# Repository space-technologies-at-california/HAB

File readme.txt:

High Altitude Balloon Team
Space Technologies at Cal
University of California, Berkeley

We're currently working on HABV!

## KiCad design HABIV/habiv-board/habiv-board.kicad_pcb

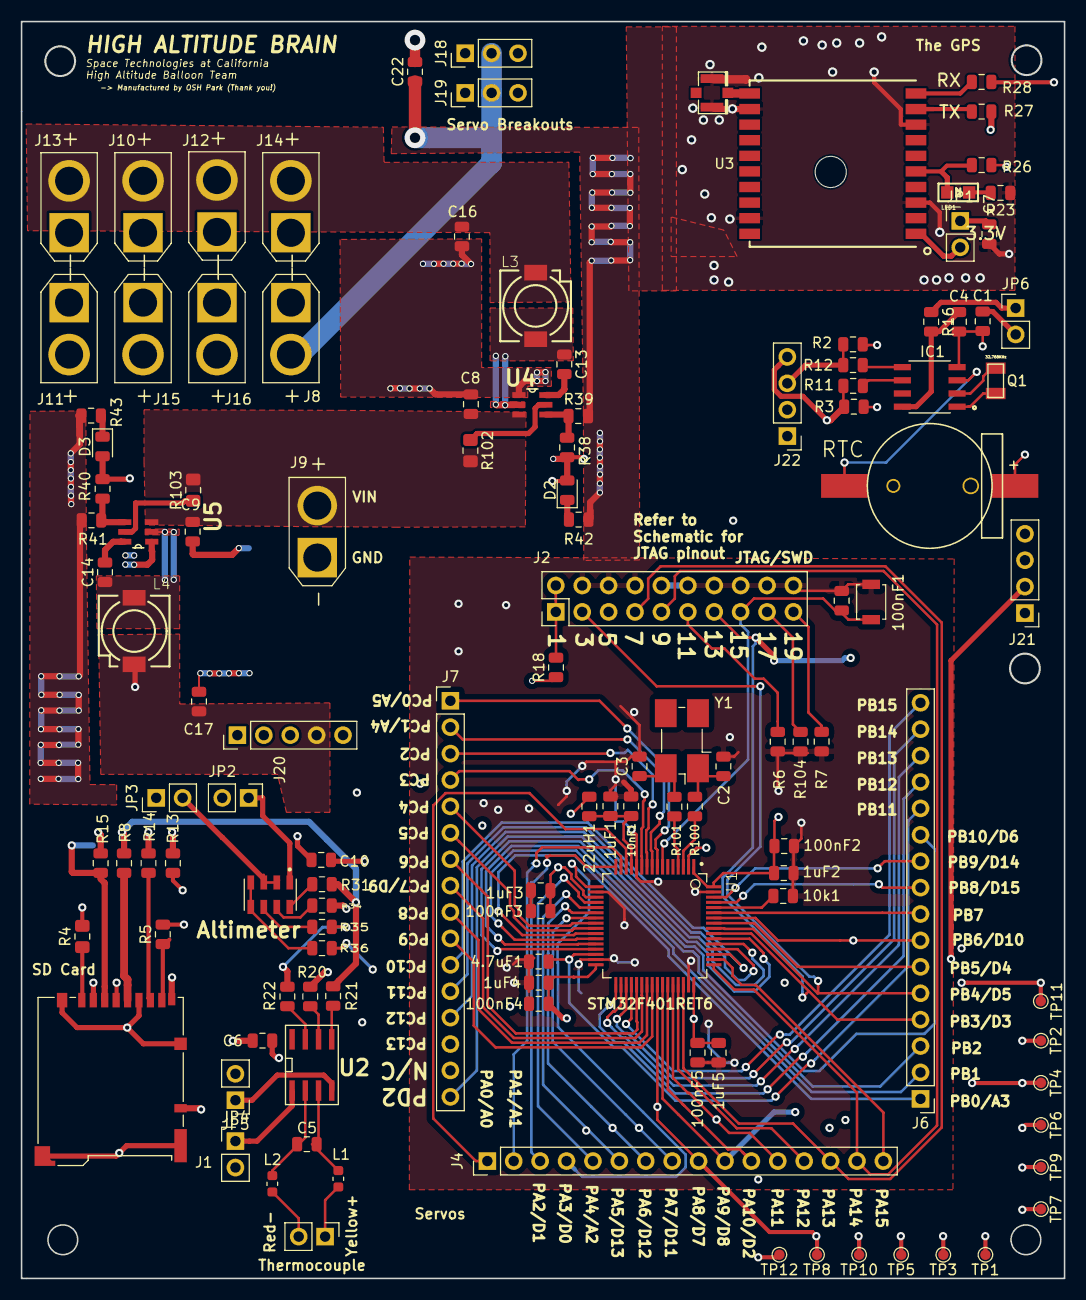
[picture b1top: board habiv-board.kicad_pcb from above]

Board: 4 copper layers, 100.3 x 120.9 mm, 122 parts (0 on the bottom side), 106 nets.

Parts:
1uF1: C6; C_0805_2012Metric
1uF2: C14; C_0805_2012Metric
1uF3: C8; C_0805_2012Metric
1uF4: C12; C_0805_2012Metric
1uF5: C10; C_0805_2012Metric
4.7uF1: C21; C_0805_2012Metric
10k1: R5; R_0805_2012Metric
10nF1: C7; C_0805_2012Metric
22uH1: L1; L_0805_2012Metric
100nF1: C5; C_0805_2012Metric
100nF2: C15; C_0805_2012Metric
100nF3: C9; C_0805_2012Metric
100nF4: C13; C_0805_2012Metric
100nF5: C11; C_0805_2012Metric
B2: CR1220; S8411-45R
C1, C22: 10u; C_0805_2012Metric
C2, C3: 4.3pF; C_0805_2012Metric
C4: 3.3uF; C_0805_2012Metric
C5: .01 uF; C_0805_2012Metric
C6: 0.1 uF; C_0805_2012Metric
C7: 0.1u; C_0805_2012Metric
C8, C9: 10uF; C_0805_2012Metric
C10, C13, C14: 100nF; C_0805_2012Metric
C16, C17: 47uF; C_0805_2012Metric
D2, D3: LED; LED_0805_2012Metric
IC1: RTC_PCF8523T; SOIC127P600X175-8N
J1: Micro_SD_Card_Det; microSD_HC_Hirose_DM3BT-DSF-PEJS
J2: Conn_ARM_JTAG_SWD_20; PinHeader_2x10_P2.54mm_Vertical
J3: Conn_01x02_Male; PinHeader_1x02_P2.54mm_Vertical
J4, J6, J7: Conn_01x16_Male; PinHeader_1x16_P2.54mm_Vertical
J8, J10, J11, J12, J13, J14, J15, J16: Conn_01x02_Female; AMASS_XT30U-F_1x02_P5.0mm_Vertical
J9: Conn_01x02_Male; AMASS_XT30U-M_1x02_P5.0mm_Vertical
J18, J19: Conn_01x03_Male; PinHeader_1x03_P2.54mm_Vertical
J20: Conn_01x05_Male; PinHeader_1x05_P2.54mm_Vertical
J21, J22: Conn_01x04_Male; PinHeader_1x04_P2.54mm_Vertical
JP1, JP2, JP3, JP4, JP5, JP6: Jumper; PinHeader_1x02_P2.54mm_Vertical
L1, L2: Ferrite_Bead; L_0603_1608Metric
L3: 2.2uH; INDC7070X450
L4: 3.3uH; INDC7070X450
LED1: RED; CHIPLED_0805
Q1: 32.768KHz; XTAL320X150X90
R2, R3: 8.2k; R_0805_2012Metric
R4: 0; R_0805_2012Metric_Pad1.15x1.40mm_HandSolder
R5, R8, R11, R12, R13, R14, R15, R18, R20, R21, R22, R26, R27, R28, R31, R34, R35, R36: 0; R_0805_2012Metric
R6, R7, R104: 10K; R_0805_2012Metric
R16, R23: 1K; R_0805_2012Metric
R38: 33.2k; R_0805_2012Metric
R39, R41: 10k; R_0805_2012Metric
R40: 56.2k; R_0805_2012Metric
R42, R43: 4.7k; R_0805_2012Metric
R100: 0k1; R_0805_2012Metric
R101: 0k2; R_0805_2012Metric
R102, R103: 10K; R_0805_2012Metric_Pad1.15x1.40mm_HandSolder
SW1: SW_DPST_x2; SW_SPST_B3U-1000P
TP1, TP2, TP3, TP4, TP5, TP6, TP7, TP8, TP9, TP10, TP11, TP12: TestPoint; TestPoint_Pad_D1.0mm
U1: STM32F401RET6; QFP50P1200X1200X160-64N
U2: MAX31855; SO-8
U3: FGPMMOPA6H
U4, U5: TPS564208
U7: MS560702BA03-00; SON125P500X300X100-8N
U$1: U.FL
Y1: 32.768MHz; Crystal_SMD_0603-4Pin_6.0x3.5mm_HandSoldering

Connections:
+3V3: 1uF2.2, 1uF3.2, 1uF4.2, 1uF5.2, 22uH1.2, 100nF2.2, 100nF3.2, 100nF4.2, 100nF5.2, C1.1, C6.2, C7.1, C10.1, C16.1, D2.2, J1.4, J10.2, J12.2, J13.2, J14.2, J21.4, J22.2, JP1.1, JP2.2, JP5.2, JP6.2, L3.1, R2.1, R3.1, R4.2, R5.2, R18.1, R38.2, U1.1, U1.19, U1.32, U1.48, U1.64
+5V: C17.1, C22.1, D3.2, J8.2, J11.2, J15.2, J16.2, J18.2, J19.2, J20.4, L4.1, R40.2
GND: 1uF1.1, 1uF2.1, 1uF3.1, 1uF4.1, 1uF5.1, 4.7uF1.1, 10k1.2, 10nF1.1, 100nF1.2, 100nF2.1, 100nF3.1, 100nF4.1, 100nF5.1, B2.1, C1.2, C2.2, C3.2, C4.2, C6.1, C7.2, C8.2, C9.2, C10.2, C16.2, C17.2, C22.2, IC1.4, J1.6, J1.11, J2.4, J2.6, J2.8, J2.10, J2.12, J2.14, J2.16, J2.18, J2.20, J8.1, J9.1, J10.1, J11.1, J12.1, J13.1, J14.1, J15.1, J16.1, J18.1, J19.1, J20.5, J21.1, J22.1, JP3.1, JP4.2, R6.1, R7.1, R23.1, R39.1, R41.1, R42.1, R43.1, R104.1, SW1.1, U1.12, U1.18, U1.31, U1.47, U1.63, U3.P$3, U3.P$8, U3.P$12, U3.P$19, U4.1, U5.1, U$1.P$1, U$1.P$2
unnamed: 10k1.1, U1.60
unnamed: 1uF1.2, 10nF1.2, 22uH1.1, U1.13
unnamed: B2.2, IC1.3
unnamed: C2.1, R100.2, Y1.1
unnamed: C3.1, R101.2, Y1.4
unnamed: C4.1, IC1.8, R16.2
unnamed: C5.1, L1.1, U2.3
unnamed: C5.2, L2.1, U2.2
unnamed: C8.1, C9.1, J9.2, R102.2, R103.2, U4.3, U5.3
unnamed: C13.1, L3.2, U4.2
unnamed: C13.2, U4.6
unnamed: C14.1, L4.2, U5.2
unnamed: C14.2, U5.6
unnamed: D2.1, R42.2
unnamed: D3.1, R43.2
unnamed: IC1.1, Q1.1
unnamed: IC1.2, Q1.2
unnamed: IC1.5, R12.1
unnamed: IC1.6, R11.1
unnamed: J1.1, R4.1
unnamed: J1.2, R13.2
unnamed: J1.3, R15.2
unnamed: J1.5, R8.1
unnamed: J1.7, R14.1
unnamed: J1.8, R5.1
unnamed: J2.1, J2.2, R18.2
unnamed: J2.11, R6.2
unnamed: J2.17, R104.2
unnamed: J2.19, R7.2
unnamed: J3.1, L1.2
unnamed: J3.2, L2.2
unnamed: JP1.2, U3.P$1
unnamed: JP2.1, U7.1
unnamed: JP3.2, U7.2, U7.3
unnamed: JP4.1, U2.1
unnamed: JP5.1, U2.4
unnamed: JP6.1, R16.1
unnamed: LED1.A, R26.1, U3.P$5
unnamed: LED1.C, R23.2
unnamed: R20.1, U2.6
unnamed: R21.1, U2.5
unnamed: R22.1, U2.7
unnamed: R27.1, U3.P$9
unnamed: R28.1, U3.P$10
unnamed: R31.1, U7.8
unnamed: R34.1, U7.7
unnamed: R35.1, U7.6
unnamed: R36.2, U7.4, U7.5
unnamed: R38.1, R39.2, U4.4
unnamed: R40.1, R41.2, U5.4
unnamed: R100.1, U1.3
unnamed: R101.1, U1.4
unnamed: R102.1, U4.5
unnamed: R103.1, U5.5
unnamed: U3.P$11, U$1.P$3
PA0: J4.1, U1.14
PA1: J4.2, U1.15
PA2: J4.3, U1.16
PA3: J4.4, R13.1, TP6.1, U1.17
PA4: J4.5, U1.20
PA5: J4.6, R8.2, R21.2, R31.2, TP4.1, U1.21
PA6: J4.7, R14.2, R22.2, R35.2, TP3.1, U1.22
PA7: J4.8, R15.1, R34.2, TP5.1, U1.23
PA8: J4.9, R36.1, TP8.1, U1.41
PA9: J4.10, J19.3, U1.42
PA10: J4.11, J18.3, U1.43
PA11: J4.12, J20.2, U1.44
PA12: J4.13, J20.1, U1.45
PA13: J2.7, J4.14, U1.46
PA14: J2.9, J4.15, U1.49
PA15: J2.5, J4.16, U1.50
PB0: J6.1, U1.26
PB1: J6.2, U1.27
PB2: J6.3, U1.28
PB3: J2.13, J6.4, J21.3, U1.55
PB4: J2.3, J6.5, TP11.1, U1.56
PB5: J6.6, J21.2, U1.57
PB6: J6.7, R28.2, TP10.1, U1.58
PB7: J6.8, R27.2, TP9.1, U1.59
PB8: J6.9, J22.4, R3.2, R11.2, TP1.1, U1.61
PB9: J6.10, J22.3, R2.2, R12.2, TP2.1, U1.62
PB10: J6.11, J20.3, U1.29
PB11: 4.7uF1.2, J6.12, U1.30
PB12: J6.13, U1.33
PB13: J6.14, U1.34
PB14: J6.15, U1.35
PB15: J6.16, R26.2, U1.36
PC0: J1.10, J7.1, U1.8
PC1: J1.9, J7.2, U1.9
PC2: J7.3, U1.10
PC3: J7.4, U1.11
PC4: J7.5, U1.24
PC5: J7.6, U1.25
PC6: J7.7, U1.37
PC7: J7.8, R20.2, TP7.1, U1.38
PC8: J7.9, U1.39
PC9: J7.10, U1.40
PC10: J7.11, U1.51
PC11: J7.12, U1.52
PC12: J7.13, U1.53
PC13: J7.14, U1.2
PD2: J7.16, U1.54
RST: 100nF1.1, J2.15, SW1.2, TP12.1, U1.7

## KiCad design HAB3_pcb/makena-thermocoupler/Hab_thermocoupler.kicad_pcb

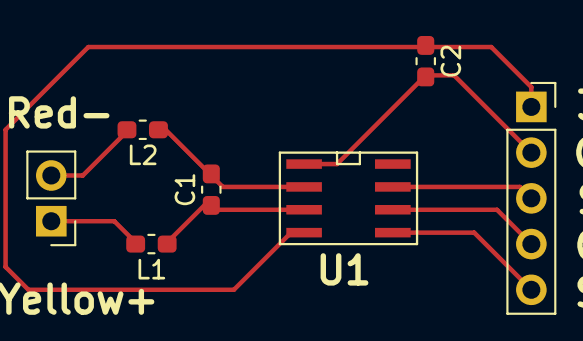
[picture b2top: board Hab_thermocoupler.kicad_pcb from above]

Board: 4 copper layers, 7 parts (0 on the bottom side), 9 nets.

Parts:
C1: .01 uF; C_0603_1608Metric_Pad1.05x0.95mm_HandSolder
C2: 0.1 uF; C_0603_1608Metric_Pad1.05x0.95mm_HandSolder
J1: Conn_01x02_Male; PinHeader_1x02_P2.54mm_Vertical
J2: Conn_01x05_Female; PinSocket_1x05_P2.54mm_Vertical
L1, L2: Ferrite_Bead; L_0603_1608Metric_Pad1.05x0.95mm_HandSolder
U1: MAX31855; SO-8

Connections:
+3V3: C2.1, J2.1, U1.4
unnamed: C1.1, L1.1, U1.3
unnamed: C1.2, L2.1, U1.2
unnamed: C2.2, J2.2, U1.1
unnamed: J1.1, L1.2
unnamed: J1.2, L2.2
unnamed: J2.3, U1.7
unnamed: J2.4, U1.6
unnamed: J2.5, U1.5

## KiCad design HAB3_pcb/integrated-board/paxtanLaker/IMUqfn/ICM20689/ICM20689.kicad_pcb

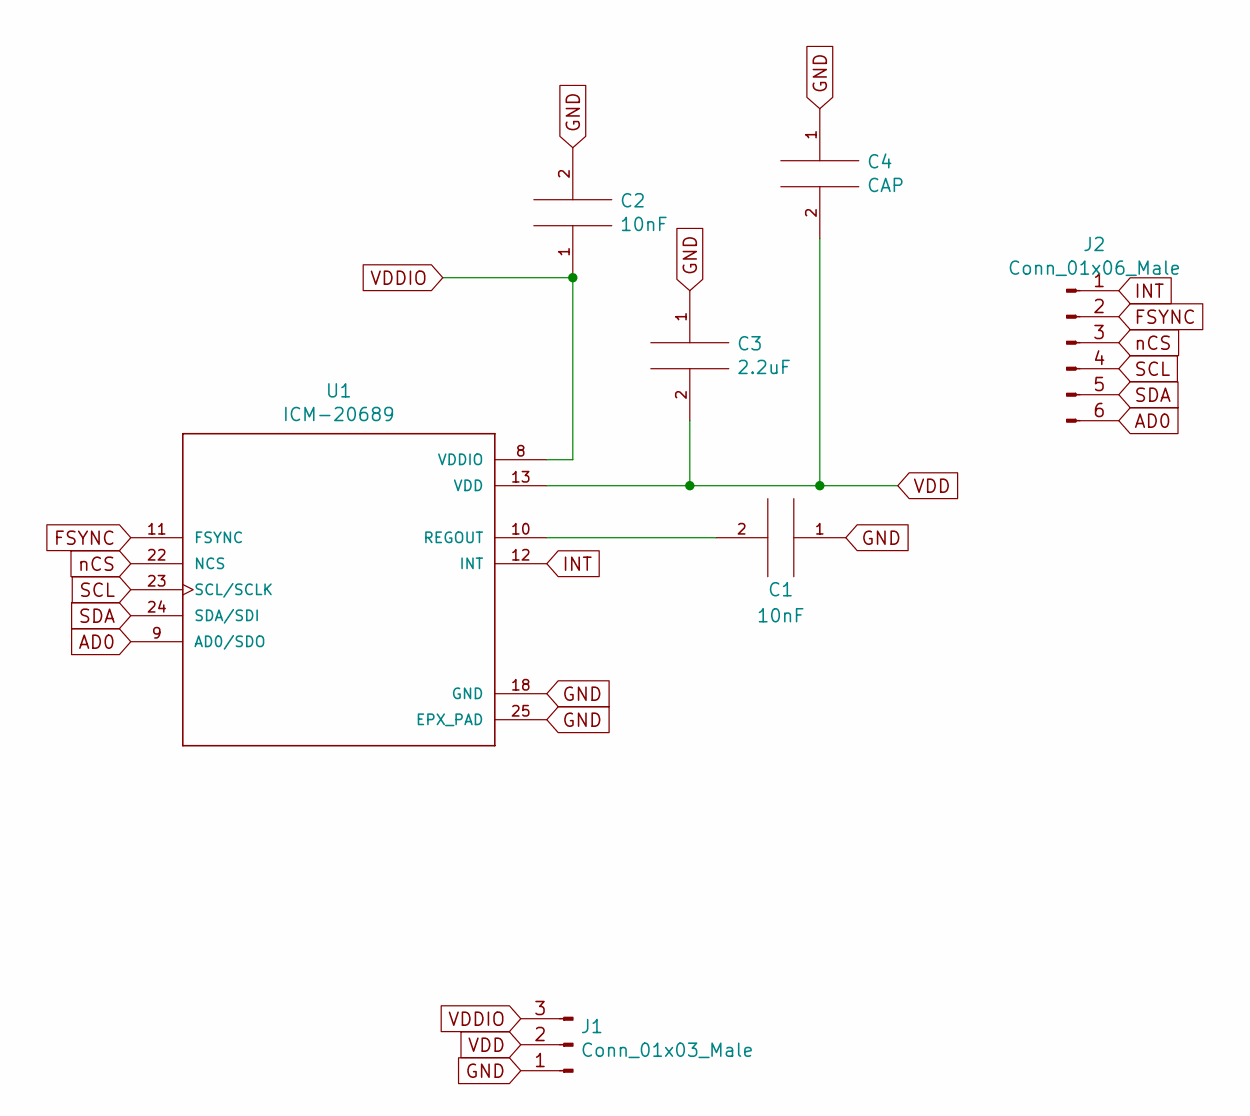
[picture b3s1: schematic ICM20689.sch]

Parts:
C1, C2: 10nF; C_0603_1608Metric_Pad1.05x0.95mm_HandSolder
C3: 2.2uF; C_0603_1608Metric_Pad1.05x0.95mm_HandSolder
C4: CAP; C_0603_1608Metric_Pad1.05x0.95mm_HandSolder
J1: Conn_01x03_Male; PinHeader_1x03_P2.54mm_Vertical
J2: Conn_01x06_Male; PinHeader_1x06_P2.54mm_Vertical
U1: ICM-20689; QFN50P400X400X95-25N

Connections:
AD0: J2.6, U1.9 (AD0/SDO)
FSYNC: J2.2, U1.11 (FSYNC)
GND: C1.1, C2.2, C3.1, C4.1, J1.1, U1.18 (GND), U1.25 (EPX_PAD)
INT: J2.1, U1.12 (INT)
unnamed: C1.2, U1.10 (REGOUT)
SCL: J2.4, U1.23 (SCL/SCLK)
SDA: J2.5, U1.24 (SDA/SDI)
VDD: C3.2, C4.2, J1.2, U1.13 (VDD)
VDDIO: C2.1, J1.3, U1.8 (VDDIO)
nCS: J2.3, U1.22 (NCS)

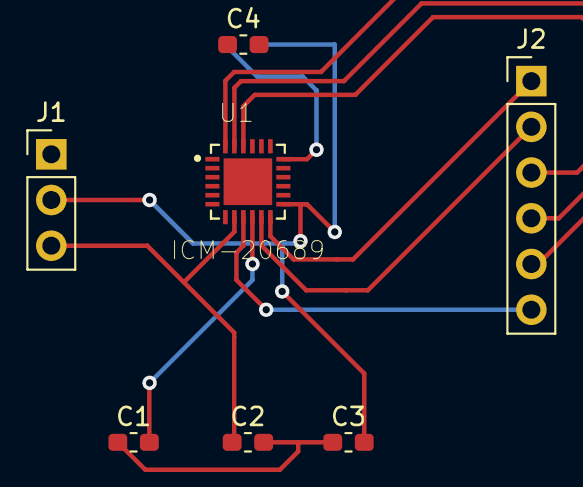
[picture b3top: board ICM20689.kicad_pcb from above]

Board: 2 copper layers, 7 parts (0 on the bottom side), 10 nets.

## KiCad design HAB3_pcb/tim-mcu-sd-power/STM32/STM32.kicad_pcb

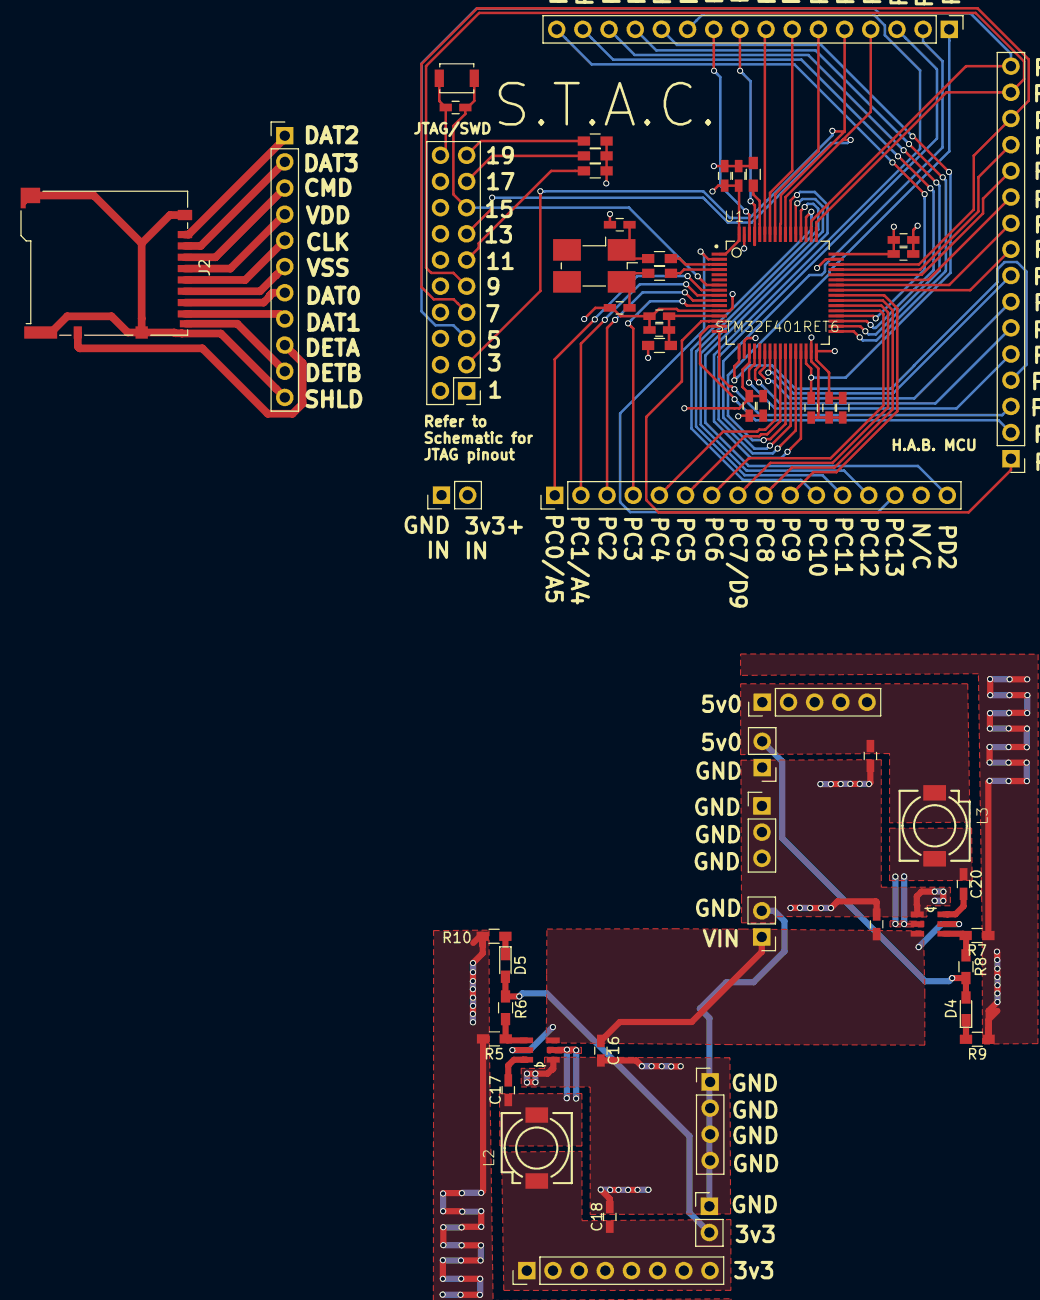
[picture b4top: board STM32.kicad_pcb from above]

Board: 4 copper layers, 56 parts (0 on the bottom side), 82 nets.

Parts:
0k1: R1; R_0603_HandSoldering
0k2: R2; R_0603_HandSoldering
1uF1: C6; C_0603_HandSoldering
1uF2: C14; C_0603_HandSoldering
1uF3: C8; C_0603_HandSoldering
1uF4: C12; C_0603_HandSoldering
1uF5: C10; C_0603_HandSoldering
4.7uF1: C21; C_0603_HandSoldering
10k1: R6; R_0603_HandSoldering
10k2: R7; R_0603_HandSoldering
10k3: R8; R_0603_HandSoldering
10k4: R5; R_0603_HandSoldering
10nF1: C7; C_0603_HandSoldering
22uH1: L1; L_0603_HandSoldering
100nF1: C5; C_0603_HandSoldering
100nF2: C15; C_0603_HandSoldering
100nF3: C9; C_0603_HandSoldering
100nF4: C13; C_0603_HandSoldering
100nF5: C11; C_0603_HandSoldering
C1, C2: 4.3pF; C_0603_HandSoldering
C16, C19: 10uF; C_0603_HandSoldering
C17, C20: 100nF; C_0603_HandSoldering
C18, C21: 47uF; C_0603_HandSoldering
D4, D5: LED; LED_0603_HandSoldering
J1: Conn_ARM_JTAG_SWD_20; Pin_Header_Straight_2x10_Pitch2.54mm
J2: Micro_SD_Card_Det; Hirose_DM3BT-DSF-PEJS
J3, J4, J5: Conn_01x16_Male; Pin_Header_Straight_1x16_Pitch2.54mm
J6, J7, J8, J10: Conn_01x02_Male; Pin_Header_Straight_1x02_Pitch2.54mm
J9: Conn_01x11_Male; Pin_Header_Straight_1x11_Pitch2.54mm
J12: Conn_01x03_Male; Pin_Header_Straight_1x03_Pitch2.54mm
J13: Conn_01x04_Male; Pin_Header_Straight_1x04_Pitch2.54mm
J14: Conn_01x05_Male; Pin_Header_Straight_1x05_Pitch2.54mm
J15: Conn_01x08_Male; Pin_Header_Straight_1x08_Pitch2.54mm
L2: 2.2uH; INDC7070X450
L3: 3.3uH; INDC7070X450
R5, R7: 10k; R_0603_HandSoldering
R6: 33.2k; R_0603_HandSoldering
R8: 56.2k; R_0603_HandSoldering
R9, R10: 4.7k; R_0603_HandSoldering
SW1: SW_DPST_x2; SW_SPST_B3U-1000P
U1: STM32F401RET6; QFP50P1200X1200X160-64N
U2, U3: TPS564208
Y1: 32.768MHz; Crystal_SMD_0603-4pin_6.0x3.5mm_HandSoldering

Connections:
+3.3VA: 1uF1.2, 10nF1.2, 22uH1.1, U1.13
+3V3: 1uF2.2, 1uF3.2, 1uF4.2, 1uF5.2, 22uH1.2, 100nF2.2, 100nF3.2, 100nF4.2, 100nF5.2, J1.1, J1.2, J6.2, U1.1, U1.19, U1.32, U1.48, U1.64
GND: 1uF1.1, 1uF2.1, 1uF3.1, 1uF4.1, 1uF5.1, 4.7uF1.1, 10k1.1, 10k2.1, 10k3.1, 10k4.2, 10nF1.1, 100nF1.2, 100nF2.1, 100nF3.1, 100nF4.1, 100nF5.1, C1.2, C2.2, J1.4, J1.6, J1.8, J1.10, J1.12, J1.14, J1.16, J1.18, J1.20, J6.1, SW1.1, U1.12, U1.18, U1.31, U1.47, U1.63
unnamed: 0k1.1, U1.3
unnamed: 0k1.2, C1.1, Y1.1
unnamed: 0k2.1, U1.4
unnamed: 0k2.2, C2.1, Y1.4
unnamed: 10k1.2, J1.11
unnamed: 10k2.2, J1.19
unnamed: 10k3.2, J1.17
unnamed: 10k4.1, U1.60
unnamed: C16.1, C19.1, J7.1, U2.3, U2.5, U3.3, U3.5
unnamed: C16.2, C18.2, C19.2, C21.2, J7.2, J8.1, J10.1, J12.1, J12.2, J12.3, J13.1, J13.2, J13.3, J13.4, R5.1, R7.1, R9.1, R10.1, U2.1, U3.1
unnamed: C17.1, L2.2, U2.2
unnamed: C17.2, U2.6
unnamed: C18.1, D5.2, J8.2, J15.1, J15.2, J15.3, J15.4, J15.5, J15.6, J15.7, J15.8, L2.1, R6.2
unnamed: C20.1, L3.2, U3.2
unnamed: C20.2, U3.6
unnamed: C21.1, D4.2, J10.2, J14.1, J14.2, J14.3, J14.4, J14.5, L3.1, R8.2
unnamed: D4.1, R9.2
unnamed: D5.1, R10.2
unnamed: J2.1, J9.1
unnamed: J2.2, J9.2
unnamed: J2.3, J9.3
unnamed: J2.4, J9.4
unnamed: J2.5, J9.5
unnamed: J2.6, J9.6
unnamed: J2.7, J9.7
unnamed: J2.8, J9.8
unnamed: J2.9, J9.10
unnamed: J2.10, J9.9
unnamed: J2.11, J9.11
unnamed: R5.2, R6.1, U2.4
unnamed: R7.2, R8.1, U3.4
PA0: J3.1, U1.14
PA1: J3.2, U1.15
PA2: J3.3, U1.16
PA3: J3.4, U1.17
PA4: J3.5, U1.20
PA5: J3.6, U1.21
PA6: J3.7, U1.22
PA7: J3.8, U1.23
PA8: J3.9, U1.41
PA9: J3.10, U1.42
PA10: J3.11, U1.43
PA11: J3.12, U1.44
PA12: J3.13, U1.45
PA13: J1.7, J3.14, U1.46
PA14: J1.9, J3.15, U1.49
PA15: J1.5, J3.16, U1.50
PB0: J4.1, U1.26
PB1: J4.2, U1.27
PB2: J4.3, U1.28
PB3: J1.13, J4.4, U1.55
PB4: J1.3, J4.5, U1.56
PB5: J4.6, U1.57
PB6: J4.7, U1.58
PB7: J4.8, U1.59
PB8: J4.9, U1.61
PB9: J4.10, U1.62
PB10: J4.11, U1.29
PB11: 4.7uF1.2, J4.12, U1.30
PB12: J4.13, U1.33
PB13: J4.14, U1.34
PB14: J4.15, U1.35
PB15: J4.16, U1.36
PC0: J5.1, U1.8
PC1: J5.2, U1.9
PC2: J5.3, U1.10
PC3: J5.4, U1.11
PC4: J5.5, U1.24
PC5: J5.6, U1.25
PC6: J5.7, U1.37
PC7: J5.8, U1.38
PC8: J5.9, U1.39
PC9: J5.10, U1.40
PC10: J5.11, U1.51
PC11: J5.12, U1.52
PC12: J5.13, U1.53
PC13: J5.14, U1.2
PD2: J5.16, U1.54
RST: 100nF1.1, J1.15, SW1.2, U1.7

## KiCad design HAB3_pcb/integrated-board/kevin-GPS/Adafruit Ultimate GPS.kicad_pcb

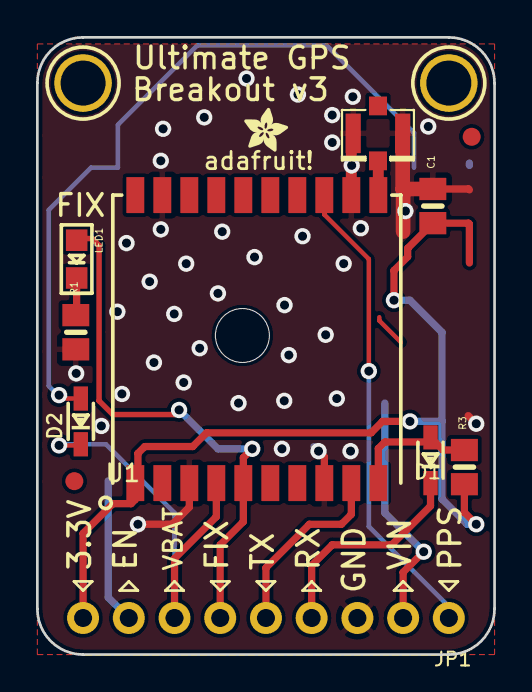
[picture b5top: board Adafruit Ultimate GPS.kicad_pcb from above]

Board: 4 copper layers, 25.4 x 34.3 mm, 17 parts (0 on the bottom side), 11 nets.

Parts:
B1: CR1220
C1: 0.1uF; 0805-NO
D1: 1N4148; SOD-323
D2: CUS520; SOD-323
FID1, FID2: FIDUCIAL; FIDUCIAL_1MM
JP1: HEADER-1X970MIL; 1X09_ROUND_70
LED1: RED; CHIPLED_0805
R1: 1K; 0805-NO
R3: 10K; 0805-NO
U1: FGPMMOPA6H
U$8, U$9: MOUNTINGHOLE2.5; MOUNTINGHOLE_2.5_PLATED
U$15: ADAFRUIT_2.5MM
U$16: PCBFEAT-REV-040
U$18: ADAFRUIT_5MM
U$20: U.FL

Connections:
3.3V: C1.1, JP1.9, R3.1, U1.P$1
/1PPS: JP1.1, U1.P$13
/FIX: JP1.6, LED1.A, U1.P$5
/RX: D1.C, JP1.4
/RX_3V: D1.A, R3.2, U1.P$10
/TX: JP1.5, U1.P$9
/VBACKUP: D2.C, JP1.7, U1.P$4
GND: B1.-, C1.2, JP1.3, R1.1, U1.P$3, U1.P$8, U1.P$12, U1.P$19, U$20.P$1, U$20.P$2
unnamed: B1.+$1, B1.+$2, D2.A
unnamed: LED1.C, R1.2
unnamed: U1.P$11, U$20.P$3

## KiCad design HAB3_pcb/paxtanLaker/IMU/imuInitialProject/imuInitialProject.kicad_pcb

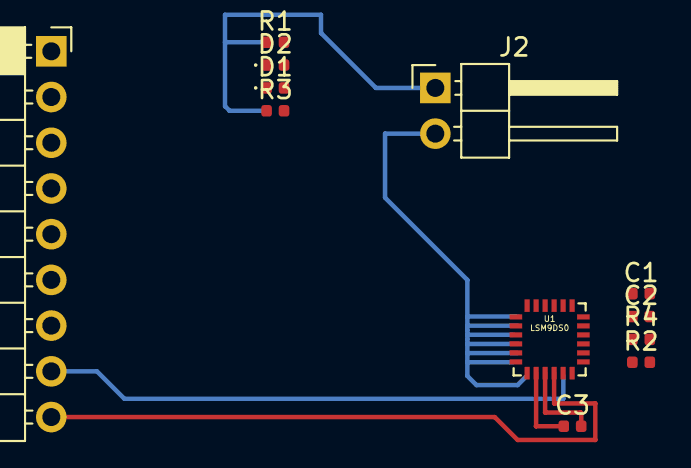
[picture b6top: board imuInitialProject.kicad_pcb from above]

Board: 2 copper layers, 12 parts (0 on the bottom side), 17 nets.

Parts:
C1: 100nF; C_0402_1005Metric
C2: 10uF; C_0402_1005Metric
C3: 0.22uF; C_0402_1005Metric
D1, D2: D_Small; D_0402_1005Metric
J1: Conn_01x09_Female; PinSocket_1x09_P2.54mm_Horizontal
J2: Conn_01x02_Female; PinHeader_1x02_P2.54mm_Horizontal
R1, R2, R3, R4: 10k; R_0402_1005Metric
U1: LSM9DS0; LGA-24LSM

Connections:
unnamed: C1.1, C2.1, J2.2, U1.2, U1.3, U1.4, U1.5, U1.6, U1.7
unnamed: C1.2, C2.2, J2.1, R1.1, R2.1, R3.1, R4.2, U1.15, U1.16, U1.17, U1.18
unnamed: C3.1, U1.8
unnamed: C3.2, U1.9
unnamed: D1.1, J1.4
unnamed: D1.2, R1.2, U1.19
unnamed: D2.1, J1.3
unnamed: D2.2, R4.1, U1.20
unnamed: J1.1, U1.24
unnamed: J1.2, U1.21
unnamed: J1.5, U1.14
unnamed: J1.6, U1.13
unnamed: J1.7, U1.12
unnamed: J1.8, U1.11
unnamed: J1.9, U1.10
unnamed: R2.2, U1.22
unnamed: R3.2, U1.23

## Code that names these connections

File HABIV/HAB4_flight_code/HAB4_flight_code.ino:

/**
   HAB4 flight code.

   Includes functions for recieving data,
   writing it to the SD card,
   and the main control loop.

   Originally based from the HAB3 flight code.


   BOARD: GENERIC STM32F4 SERIES
   BLACK F407VE


   THIS FILE WILL INCLUDE ALL OF THE GLOBAL VARIABLES AND DEFINITIONS.

*/
#include <IridiumSBD.h>
#include <Adafruit_GPS.h>
#include "Adafruit_MAX31855.h"
#include <SPI.h>
#include <Wire.h>
#include "RTClib.h"
#include <SD.h>
#include "Servo.h"
#include <AutoPID.h>
#include "Math.h"

#include "IntersemaBaro.h"

#include "I2C_Anything.h"

#include <Adafruit_LSM9DS1.h>
#include <Adafruit_Sensor.h>

#define LOG_FILE "datalog.txt"
#define DATA_DELAY_TIME 10000

#define DIAGNOSTICS false // Iridium Diagnostics
#define GPSECHO true     // GPS Diagnostics

//Define serial communication pins
#define IridiumRX PA12
#define IridiumTX PA11

#define GPSRX PB0
#define GPSTX PB1

//#include "SoftwareSerial.h" //FOR XBEE

#define IridiumSleep PB10

#define CTR1 PC12
#define CTR2 PC13

//Define IMU pins
// SDO_XM and SDO_G are both pulled high, so our addresses are:
#define LSM9DS1_M  0x1E // Would be 0x1C if SDO_M is LOW <---EDIT WITH CORRECT VALUES
#define LSM9DS1_AG  0x6B // Would be 0x6A if SDO_AG is LOW <---EDIT WITH CORRECT VALUES
#define DECLINATION 13.25 // https://www.ngdc.noaa.gov/geomag/calculators/magcalc.shtml#declination

//XBEE
#define XBEE_RX D6 //CHANGE! can be any 
#define XBEE_TX D7 //CHANGE!!

//SERVO
#define servoPinL PA10 //CHANGE! can be PA10, PA9, PA0, PA1 top to bottom LR
#define servoPinR PA9 //CHANGE!
#define releasePin PA0 //CHANGE!
#define SENSITIVITY 15 //sensitivity of the controls. ie, if you give the control to move 

//Define SPI slave select pins
#define altimeterChipSelect PA8 // IMPORTANT!!!!! IF THIS IS CHANGED, YOU MUST CHANGE chipSelect IN IntersemaBaro.h
#define thermocoupleChipSelect PC7
#define sdCardChipSelect PA4


// Declare Serial communication
HardwareSerial GPSSerial(GPSRX, GPSTX);
HardwareSerial IridiumSerial(IridiumRX, IridiumTX);

// Declare peripheral objects
IridiumSBD modem(IridiumSerial, IridiumSleep);
Adafruit_GPS GPS(&GPSSerial);
Intersema::BaroPressure_MS5607B baro;
Adafruit_MAX31855 thermocouple(thermocoupleChipSelect);
RTC_PCF8523 rtc;

//Declare IMU
Adafruit_LSM9DS1 lsm = Adafruit_LSM9DS1();

//COMMUNICATIONS
// RX: Arduino pin 2, XBee pin DOUT.  TX:  Arduino pin 3, XBee pin DIN
//SoftwareSerial XBee(2, 3); //CHANGE PINS <--- long range: ground to payload
//SoftwareSerial XBee(4, 5); //CHANGE PINS <--- short range: payload to balloon

HardwareSerial XBee(XBEE_RX, XBEE_TX);

#define WIRE_INPUT D7 //CHANGE!

//MOVEMENT
Servo servoRelease;
bool released = false;

//motor, should be defined elsewhere.
//#define motorPinLIn1 3 //CHANGE!
//#define motorPinLIn2 4 //CHANGE!
//
//#define motorPinRIn1 5 //CHANGE!
//#define motorPinRIn2 6 //CHANGE!

//motor constants
//#define gearRatio 488.28125

////PID STUFF
//#define OUTPUT_MIN 0 //CHANGE!
//#define OUTPUT_MAX 255 //CHANGE!
//#define KP .12 //CHANGE!
//#define KI .0003 //CHANGE!
//#define KD 0 //CHANGE!


uint32_t timer = millis();

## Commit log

2016-11-03 08 March Tues
2018-02-15 rf69 libraries
2018-02-15 added readme
2018-02-15 rf69 beacon/receiver testing code ready
2018-02-15 radiohead lib was empty
2018-02-15 updated radiohead lib readme
2018-02-15 migrated jpole_sim repo to here
2018-02-18 tested RF69 transmitter
2018-02-22 started range test code for rf69
2018-02-23 chat_demo ready to test
2018-02-23 fixed chat demo, dynamic mem allocation problem
2018-02-23 memory allocation within function vs global is different; uint8_t does not reserve 8 bits
2018-02-24 embedded sys code
2018-02-24 added thermocoupling
2018-02-24 2ndary transmitter for balloon ready for integration
2018-02-24 deleted empty RadioHead folder
2018-02-24 changed rf69 pins to mega pins
2018-02-25 hey abhi
2018-02-25 LED_debug_bank added
2018-02-25 altimeter code added
2018-02-25 really ugly code
2018-02-25 added altimeter
2018-02-25 ...it worked ;)
2018-02-25 wiring diagram 60%
2018-02-25 added libraries
2018-02-25 updated arduino alt code
2018-02-25 put RadioHead-master.zip back
2018-02-26 finished wiring diagram
2018-02-26 Changed servo pins, wrote experiment code to extend both servos (needs to be tested) and wrote servo extended to log
2018-02-28 added 2ndary transceiver
2018-02-28 changed transceiver CS pin from pin 46 to pin 44
2018-02-28 added 2nd order temp and fixed barometric eq
2018-02-28 Rewrote and tested servo code on hardware
2018-03-01 adding tracksoar source code
2018-03-01 adding preliminary untested code to do spi comm with tracksoar from Mega
2018-03-02 updated HAB_Sys
2018-03-02 changed todo
2018-03-02 added tracksoar and transceiver code independently, need to integrate the two
2018-03-02 added edge cases todo in comments
2018-03-02 changed SD & thermoCS pin
2018-03-02 SD, thermo, all i2c working
2018-03-02 hopefully added stuff
2018-03-02 fixing error in tracksoar code
2018-03-02 playing with servos
2018-03-02 servo code pre-test
2018-03-02 testing servos
2018-03-02 tested all but servo lock on timeout
2018-03-02 added tracksoar -> transceiver code
2018-03-03 changing tracksoar comm to shut off spi after comms
2018-03-03 SPI tracksoar init HIGH, ty Alan
2018-03-03 servo disable example
2018-03-03 servo_disable_test & rf69_stac fixes
2018-03-03 fixing tracksoar spi issue
2018-03-03 committing to fix merge issue in HAB_sys
2018-03-03 added tracksoar data store, servo fet disable
2018-03-03 serial python altimeter test script
2018-03-03 minor servo changes
2018-03-04 added get gps lock spi fix
2018-03-04 updated serial alt test
2018-03-04 fixing issue in tracksoar comm library
2018-03-04 CS tracksoar
2018-03-04 gps lock spi
2018-03-04 altitude test
2018-03-04 deleted extra print statements
2018-03-04 added raw altimeter bits to CSV
2018-03-04 added one line
2018-03-04 Add files via upload
    lat, long to degrees, minutes, seconds
    optional offline coordinate finder
2018-03-04 final
2018-03-04 Deleted Serial while loop
2018-03-05 adding APRS.fi data dumps to git
2018-03-07 added decoder for aprsdroid
2018-03-20 Add files via upload
    Script for the intervalometer used with hacked Canon Powershot A3100
2018-04-12 data
2018-04-12 commenting code
2018-04-13 added Eagle files for HAB-2
2018-04-13 updated gitignore and added comments to HAB board
2018-04-14 Removed .DS_Store file and changed board schematics
2018-04-14 finished schematic
2018-04-14 fixed missing servo enable connetion
2018-04-14 placed and routed hab board
2018-04-15 Added gerbers and updated thick trace
2018-04-15 removed extra files
2018-04-15 final changes
2018-04-15 arduino example for one wire reading... requires one wire and temp libraries
2018-04-21 code moved to experiment
2018-04-21 refactoring done
2018-04-22 1 servo only
2018-04-26 Added ambient temperature sensor measuring code to Hab Sys
2018-04-27 added imu setup code
2018-04-27 all sensors added
2018-10-11 Add Hab3 PCB folder
2018-10-11 adding IMU KiCa
2018-10-11 added altimeter pcb
2018-10-11 started tracing
2018-10-16 traces done without copper fills
2018-10-16 moved folder and need to add copper fills still
2018-10-18 updated labels on riley's pcb
2018-10-18 added labels and made board have 4 layers
2018-10-18 init commit for tim-mcu-sd-power
2018-10-18 moved rtc into master
2018-10-18 Final PCB IMU
2018-10-18 halfway done with power regulator
2018-10-22 changed diodes to be SOD 123 and updated footprint
2018-10-23 Finished voltage regulator
2018-10-23 Integrated board complete
2018-10-25 had to literally redo everything
2018-10-26 integrated board with new imu-dfm complete
2018-10-28 made fixes to new imu
2018-10-29 added tracksoar eagle files
2018-10-29 convert tracksoar to kicad
2018-10-29 changed schematic and footprint following design review
2018-10-29 changed footprints to be hand-soldered style
2018-10-29 changed fonts to be thicker, 0402 -> 0603_hand_solder
2018-10-29 fixed gps board
2018-10-29 fixed power on integrated board
2018-10-29 final pcb designs complete
2018-10-29 final pcb design complete with InstantDFM
2018-10-29 final final pcb design complete with InstantDFM
2018-11-13 fix typos in TempControl.ino
2018-12-02 add flight code hab3
2018-12-02 finish hab3 flight code
2018-12-03 print data recorded to serial flight_code
2018-12-03 add rockblock antenna select
2018-12-03 add zip libraries to flight code
2018-12-03 fix get signal quality bug
2018-12-03 add more printlns to flight code
2018-12-03 webapp
2018-12-03 final changes to flight code
2019-02-02 update flight code
2019-02-23 commit unsaved changes
2019-02-23 put all schematics into HABIV
2019-02-23 habiv integrated schematic w/o power
2019-02-23 add some hardwired connections
2019-03-02 some habiv schematic changes
2019-03-02 implemented IMU power and ground connection with decoupling caps
2019-03-02 SD Card connections
2019-03-02 implemented 0 ohm resistors on Vdd pins of ICs, continue to implement 0 ohms on SPI and I2C pin
2019-03-02 finished implementing 0 ohm resistors on clock pins
2019-03-02 IMU SDA and SCL pins connected to MCU
2019-03-03 some small fixes to schematic
2019-03-09 remove the pin headers to clean up the schematic; added 0 ohm connection from GPS FIX to PB15
2019-03-10 footprint layouts for capacitors and resistors
2019-03-16 change power converter output format
2019-03-16 link more footprints
2019-03-20 test out layouts for different sections
2019-03-20 get pcb design out of old
2019-04-02 add old_board_submodules and complete all but tim
2019-04-02 finish submodules and combine
2019-04-02 layout for imu
2019-04-06 fix power system layout on habiv
2019-04-06 clean up silkscreen
2019-04-06 fix gps and fix imu connections
2019-04-06 begin to route together final nets
2019-04-06 finish most of connections for 4 layer
2019-04-17 finalize rough draft board
2019-04-19 fix drc stuff for layout
2019-04-20 spread out some imu conns
2019-04-20 change hole positions
2019-04-20 fix some references
2019-04-20 fix some schematic errorS
2019-04-20 some work on layout redo
2019-04-24 :art: Fix layout connections for new schematic
2019-04-27 add back ground plane
2019-04-27 fix all drc errors
2019-04-27 add xt30 connectors
2019-05-04 add servo breakouts
2019-05-04 add breakouts for rockblock and relay
2019-05-04 add final 5v conn
2019-09-13 finsished hw2
2019-09-18 Revert "add final 5v conn"
    This reverts commit 04f0e62ac933d6a4970588d5189f4c859ce7453e.
2019-09-18 Removed false file
2019-09-22 add noise reducing caps and fix unconnected in1 plane
2019-09-22 update silkscreen text
2019-09-22 copied hab3 code to a HABIV file.
2019-09-22 Create Semi_Controlled
2019-09-22 Create newfile
2019-09-23 added basic comments.
2019-09-25 added IMU library zip
2019-10-02 added comments about what board to use.
2019-10-02 added IMU declarations and Setup.
2019-10-06 integrated IMU with pre-existing getAllData function.
2019-10-09 set imu as I2C
2019-10-19 added one servo for testing.
2019-10-23 added basic servo control with the XBee.
2019-10-25 added example sketch for showing how to control servo from XBee input.
2019-10-31 set up XBee code for running the servo control.
2019-11-03 updated getXBeeControl()
2019-11-07 added value for release.
2019-11-08 configure data for rockblock
2019-11-08 flip lat and long
2019-11-10 bug fixes, now compiles.
2019-11-11 gen stencil
2019-11-17 documentation
2019-11-17 added basic ground control code.
2019-11-17 short test onboard.
2019-11-22 renamed some files, updated hab4 code
2019-11-23 change pins
2020-02-02 deleted tracksoar
2020-02-05 fixing integrated board naming problem
2020-02-10 Turned IMU into breakout pins, minor changes, unfinished!
2020-02-11 Changed IMU pinout, fixed some grounding issues
2020-02-12 Moved RockBlock Connector, removed some Servo breakouts
2020-02-14 Added jumpers+ Rerouting
    Added Jumpers to schematic. Rerouted trace PB10 from J20 as it was generating a design rules error. Also placed some jumpers on board.
2020-02-14 Updates for rn
2020-02-14 JP on RTC
2020-02-14 Added all jumpers
2020-02-15 double checked
2020-02-15 double check 2
2020-02-15 whoops, needed to move via
2020-02-19 did some clean-up, then added a latlong distance calculator.
2020-02-19 more cleaning, latlong update.
2020-02-23 split up the code into multiple tabs, more organized.
2020-02-23 renamed, reordered, now compiles.
2020-02-24 changed order again, added motor info.
2020-03-04 added beginning of UVB file. Updated names accordingly.
2020-03-04 forgot to add controls file.
2020-03-08 added library for I2C, integrated the UVB sensor in the rest of methods.
2020-03-08 updated sensor information with the new library and I2C.
2020-11-17 prepped code for off-loading controls to different processor.
2021-04-14 first commit adding HABV
2021-04-14 added test blinker.
2021-10-03 added HABV
2021-10-10 Added web app
2021-10-17 Added rockblock.py
2021-10-17 Added main_loop.py (Work in progress...)
2021-10-17 HABV BOARD 2
2021-10-27 Unable to plot point
2021-10-31 Web app: added point-plotting ability
2021-10-31 Added functionality for plotting multiple points
2021-10-31 Attempted to add overlay feature
2021-11-07 RockBlock code works and has been tested using USB Serial.
2021-11-14 Skeleton backend code
2021-11-14 Fixed some bugs in the template
2021-11-17 Web app: added template overlays
2021-11-17 Servo control code works. Can be imported as a function.
2022-01-30 2D PID Basic setup
2022-01-30 test.
2022-02-06 timers.
2022-02-06 Updated files
2022-02-06 Added lambda code
2022-02-20 Updated code
2022-02-27 Added beagle bone's local code into v2
2022-02-27 Updated Creds
2022-02-27 Saving HABV
2022-02-27 Changed to PST
2022-02-27 Updated code locally
2022-02-27 Removed test file
2022-02-27 Removed old files/folders
2022-02-28 Removed files
2022-03-16 added test file for aws
2022-03-27 Saving HABV prototype
2022-04-03 Saving PID flight code
2022-04-03 Saving flight code
2022-04-03 Saving flightcode
2022-04-10 Main_loop works but needs to be tested
2022-04-12 Changes to servo setting
2022-10-30 New files
2022-10-30 Added PID, traj_gen
2022-11-09 Added trajectory simulator and gps simulator
2022-11-09 Added historical NASA data
2022-11-13 Updated traj_gen
2022-11-16 Updated PID and input simulator, Added main
2022-11-16 Updated input simulator
2022-11-18 added environment class
2022-11-18 Cleaned up some code in environment.py
2022-11-20 WIP TrajGen
2022-11-27 TrajGen first iteration
2022-11-27 Refactored phase 0 and phase 1 parts
2022-11-27 Minor fixes and refactoring re phase 2
2022-11-27 Docstring fixes
2022-12-18 debugged, made working prototype
2023-01-04 Revised TrajGen
2023-01-05 Cleanup and updated phase 3
